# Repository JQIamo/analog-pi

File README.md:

# analog-pi
Analog PI controller with > 10MHz bandwidth. Design by Joe Tiamsuphat.

For full documentation of the circuit, see the [manual](https://github.com/JQIamo/analog-pi/blob/master/pi/Documents/PI_Manual.pdf).
Please read the manual very carefully, especially the section "Initial Calibration" at page 14. A wrong calibration could result in damaging the circuit's output stages.

**NOTE:** The PI controller [manual](https://github.com/JQIamo/analog-pi/blob/master/pi/Documents/PI_Manual.pdf) is out of date. It should still be used as a reference, but it does not document several new features. Please look at issues [#2](https://github.com/JQIamo/analog-pi/issues/2) and [#3](https://github.com/JQIamo/analog-pi/issues/3) for more information. 

## File description

* `/fab/*`: Ready-made files for immediate fabrication. There is the main PI board (`pi_v2.5.3`), and three "shield" boards which make assembly into the box (located in `/fab/EnclosureDesign_v2.5.3_CAD`) easier. See below for description.
* `/pi/*`: Design files for the main PI board, including documentation, schematics, simulations, etc. The schematic/board layout are done in NI Multisim + Ultiboard.
* `/pi-frontpanel/*`: Eagle board files for a frontpanel "shield" board
* `/pi-pots/*`: Eagle board files for potentiometers which set the gains, output offset, sweep amplitude.
* `/pi-shield/*`: Eagle board file for adapter shield between PI board and the POTs/Frontpanel breakout boards.

Total cost is in the neighborhood of $1k per completed box (includes professionally populated PCBs, enclosure, power supply, etc.), although that number would depend on quantity ordered, whether you populate the boards yourself, etc.

## Enclosure

There is a Protocase Designer file (in `/fab/EnclosureDesign_v2.5.3_CAD`

Other auxiliary parts:

| Name | Part number | supplier |
|-------|------------|-------|
| FuseDrawer | 486-1342-ND | Digikey|
|Fuse	|F2393-ND|	Digikey|
|PwrEntry	|486-1302-ND	|Digikey
HexStandoff	|36-4802-ND|	Digikey
KnurledKnob	|226-3084-ND	|Digikey
POT Dial|	987-1002-ND	|Digikey
Isolated BNC	|ARFX1905-ND	|Digikey
PowerSupply	|179-2302-ND|	Digikey

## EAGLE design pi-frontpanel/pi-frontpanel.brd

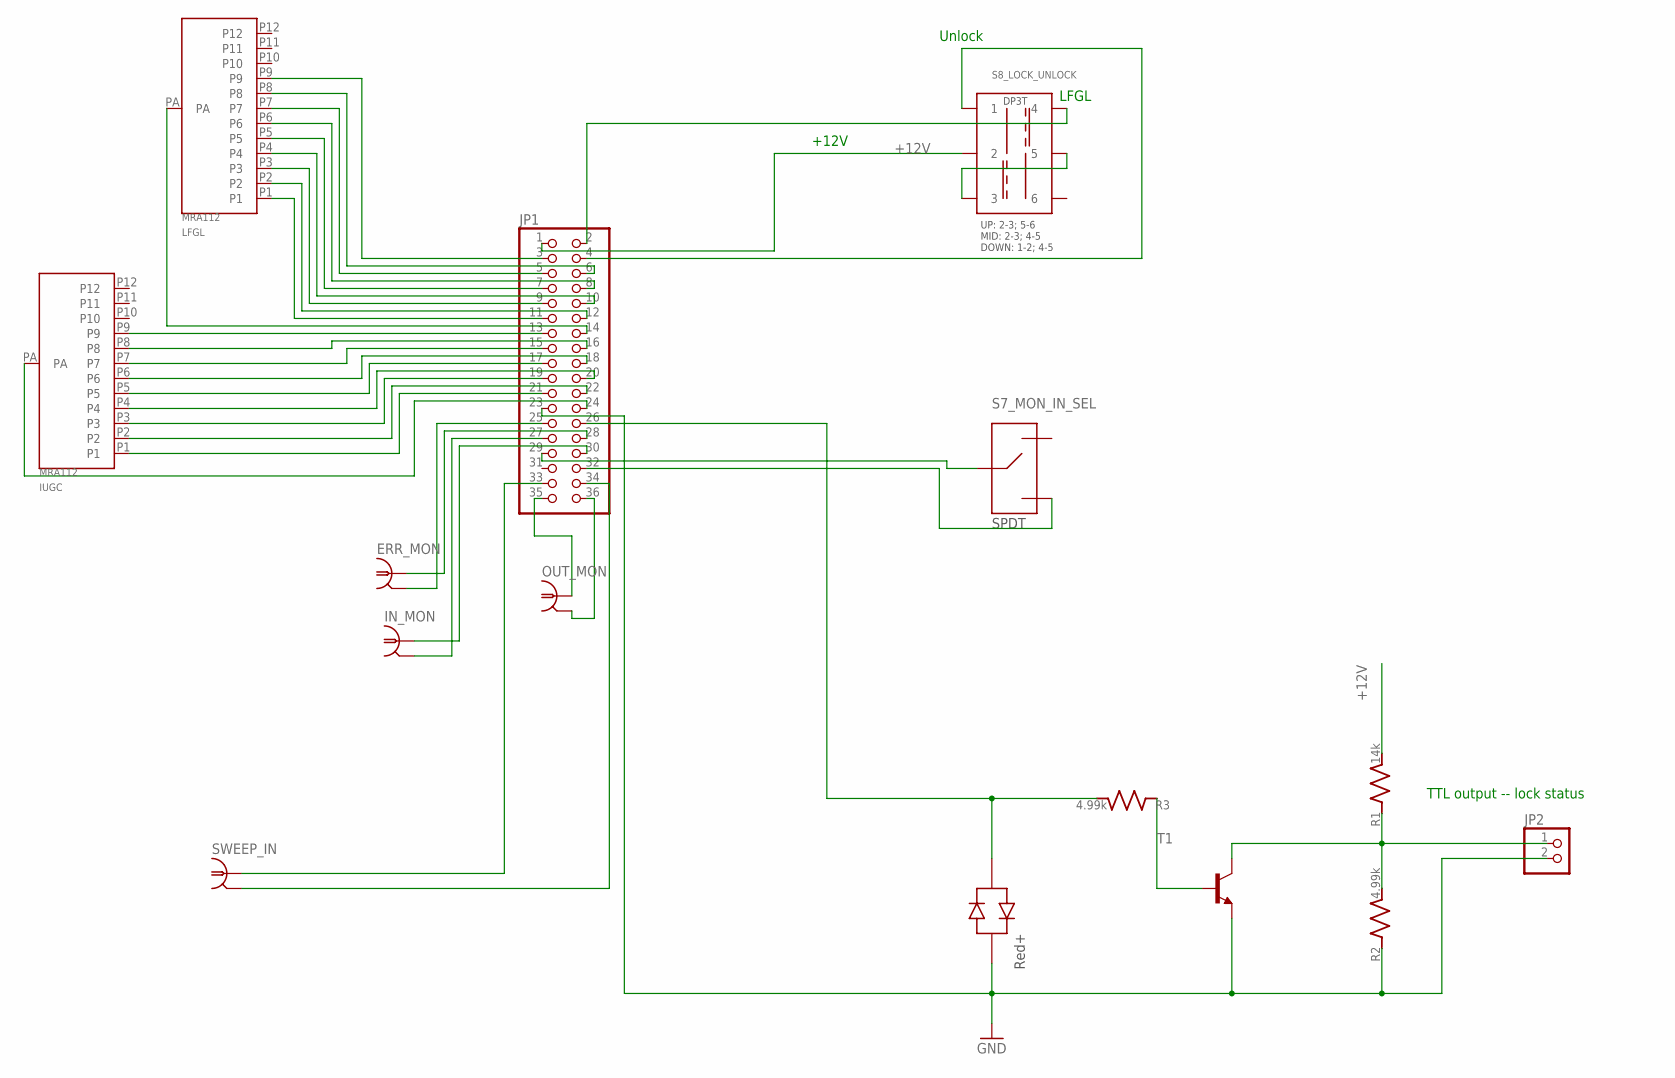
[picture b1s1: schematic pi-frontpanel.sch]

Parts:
ERR_MON: BNC-V; PARTNO A32262-ND
IN_MON: BNC-V; PARTNO A32262-ND
IUGC: MRA112; PARTNO 360-2368-ND
JP1: PINHD-2X18; 2X18; PARTNO S7086-ND
JP2: PINHD-1X2; 1X02; PARTNO A1921-ND
LED: SSL-LX5093IGW; LED-TH; PARTNO 67-2207-ND
LFGL: MRA112; PARTNO 360-2368-ND
OUT_MON: BNC-V; PARTNO A32262-ND
R1: 14k; R_1206; PARTNO P14.0KFCT-ND
R2, R3: 4.99k; R_1206; PARTNO P4.99KFCT-ND
S7_MON_IN_SEL: SPDT; SPDT_LUG; PARTNO 450-1523-ND
S8_LOCK_UNLOCK: DP3T; SP3T_LUG
SWEEP_IN: BNC-V; PARTNO A32262-ND
T1: MMBT2222ALT1-NPN-SOT23-BEC; SOT23-BEC; PARTNO MMBT2222A-FDICT-ND

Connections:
+12V: JP1.1, R1.P$2 (2), S8_LOCK_UNLOCK.2
GND: JP1.23, JP2.2, LED.P$2 (RED+), R2.P$1 (1), T1.E
unnamed: S8_LOCK_UNLOCK.3, S8_LOCK_UNLOCK.5
unnamed: JP1.3, LFGL.P9
unnamed: JP2.1, R1.P$1 (1), R2.P$2 (2), T1.C
unnamed: R3.P$1 (1), T1.B
unnamed: JP1.26, LED.P$1 (GREEN+), R3.P$2 (2)
unnamed: JP1.6, LFGL.P8
unnamed: JP1.5, LFGL.P7
unnamed: JP1.8, LFGL.P6
unnamed: JP1.7, LFGL.P5
unnamed: JP1.10, LFGL.P4
unnamed: JP1.11, LFGL.P1
unnamed: JP1.9, LFGL.P3
unnamed: JP1.12, LFGL.P2
unnamed: IUGC.P9, JP1.13
unnamed: JP1.14, LFGL.PA
unnamed: IUGC.P8, JP1.16
unnamed: IUGC.P7, JP1.15
unnamed: IUGC.P6, JP1.18
unnamed: IUGC.P5, JP1.17
unnamed: IUGC.P4, JP1.20
unnamed: IUGC.P3, JP1.19
unnamed: IUGC.P2, JP1.22
unnamed: IUGC.P1, JP1.21
unnamed: IUGC.PA, JP1.24
unnamed: IN_MON.2, JP1.27
unnamed: IN_MON.1, JP1.30
unnamed: ERR_MON.2, JP1.25
unnamed: ERR_MON.1, JP1.28
unnamed: JP1.36, OUT_MON.2
unnamed: JP1.35, OUT_MON.1
unnamed: JP1.34, SWEEP_IN.2
unnamed: JP1.33, SWEEP_IN.1
unnamed: JP1.29, S7_MON_IN_SEL.2
unnamed: JP1.32, S7_MON_IN_SEL.3
unnamed: JP1.2, S8_LOCK_UNLOCK.4
unnamed: JP1.4, S8_LOCK_UNLOCK.1

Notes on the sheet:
+12V
LFGL
Unlock
TTL output -- lock status

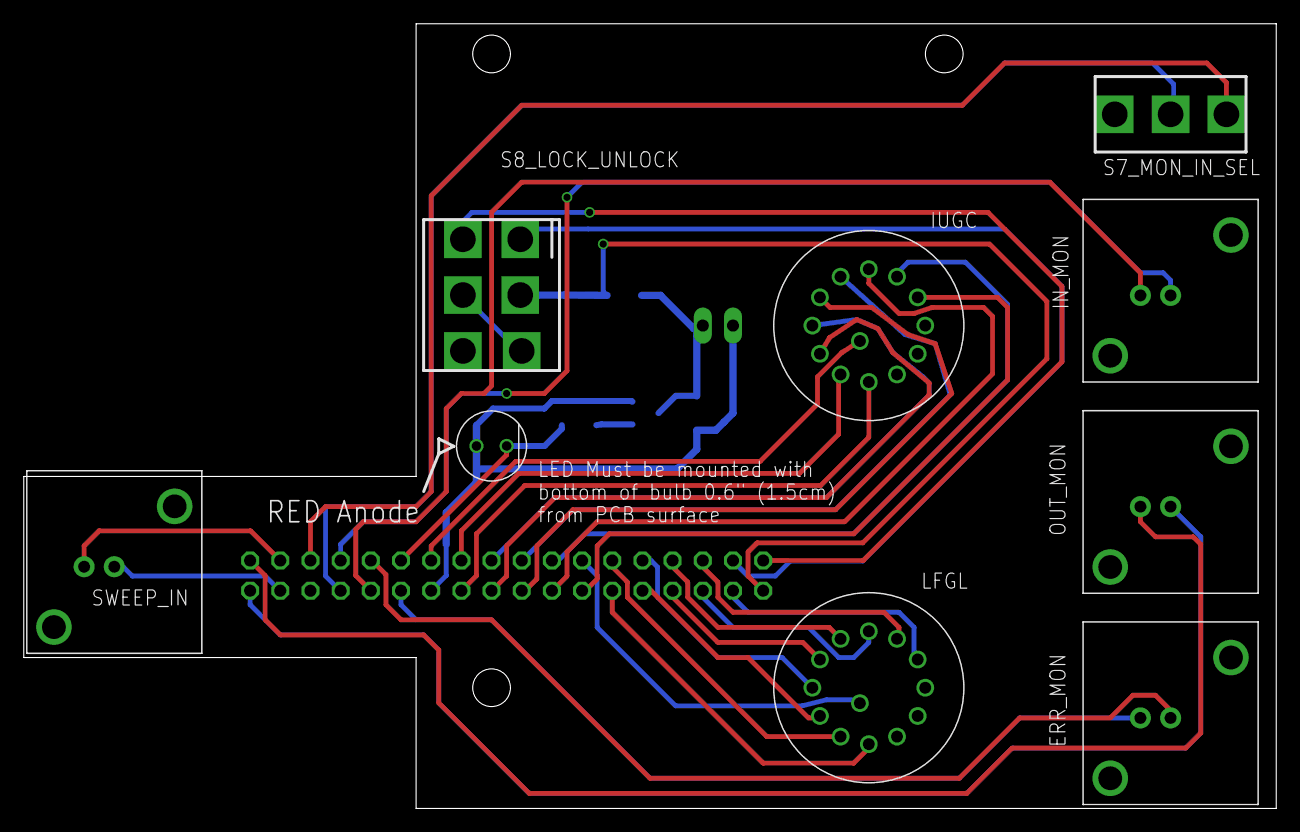
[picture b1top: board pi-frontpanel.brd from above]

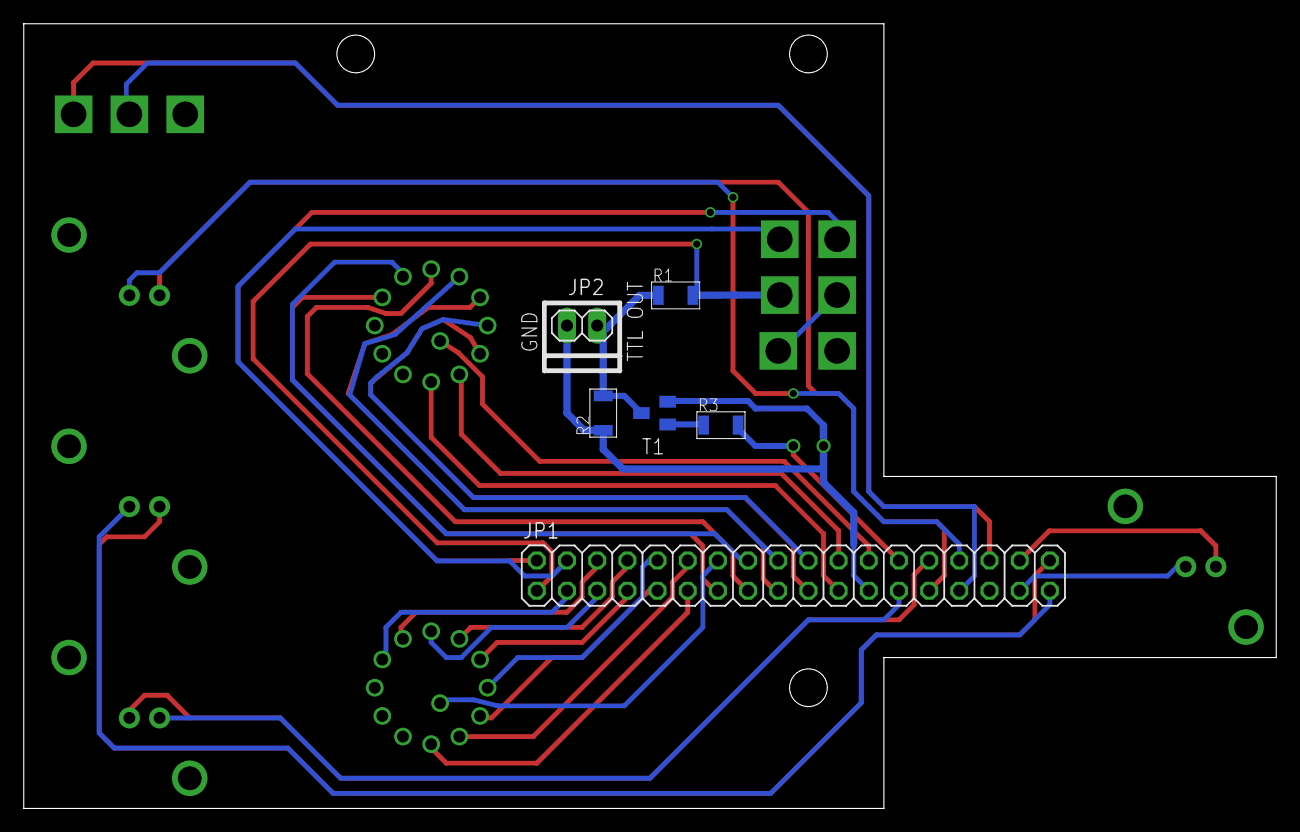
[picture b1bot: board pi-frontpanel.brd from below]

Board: 2 copper layers, 105.4 x 66.0 mm, 15 parts (6 on the bottom side), 38 nets.

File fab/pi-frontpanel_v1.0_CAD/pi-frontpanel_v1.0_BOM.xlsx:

Line | Qty | Value | Part Num | Source | Package | Parts | Notes
1.0 | 1.0 |  | 450-1536-ND | Digikey | SP3T_LUG | S8_LOCK_UNLOCK
2.0 | 1.0 |  | A1921-ND | Digikey | 1X02 | JP2
3.0 | 1.0 |  | MMBT2222A-FDICT-ND | Digikey | SOT23-BEC | T1
4.0 | 1.0 |  | S7086-ND | Digikey | 2X18 | JP1
5.0 | 2.0 | 4.99k | P4.99KFCT-ND | Digikey | R_1206 | R2, R3
6.0 | 1.0 | 14k | P14.0KFCT-ND | Digikey | R_1206 | R1
7.0 | 4.0 | BNC-V | A32262-ND | Digikey | BNC-V | ERR_MON, IN_MON, OUT_MON, SWEEP_IN
8.0 | 2.0 | MRA112 | 360-2368-ND | Digikey | MRA112 | IUGC, LFGL
9.0 | 1.0 | SPDT | 450-1523-ND | Digikey | SPDT_LUG | S7_MON_IN_SEL
10.0 | 1.0 | SSL-LX5093IGW | 67-2207-ND | Digikey | LED-TH | LED | This part needs to be soldered such that the bottom of the LED is 0.6" (1.5cm) 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

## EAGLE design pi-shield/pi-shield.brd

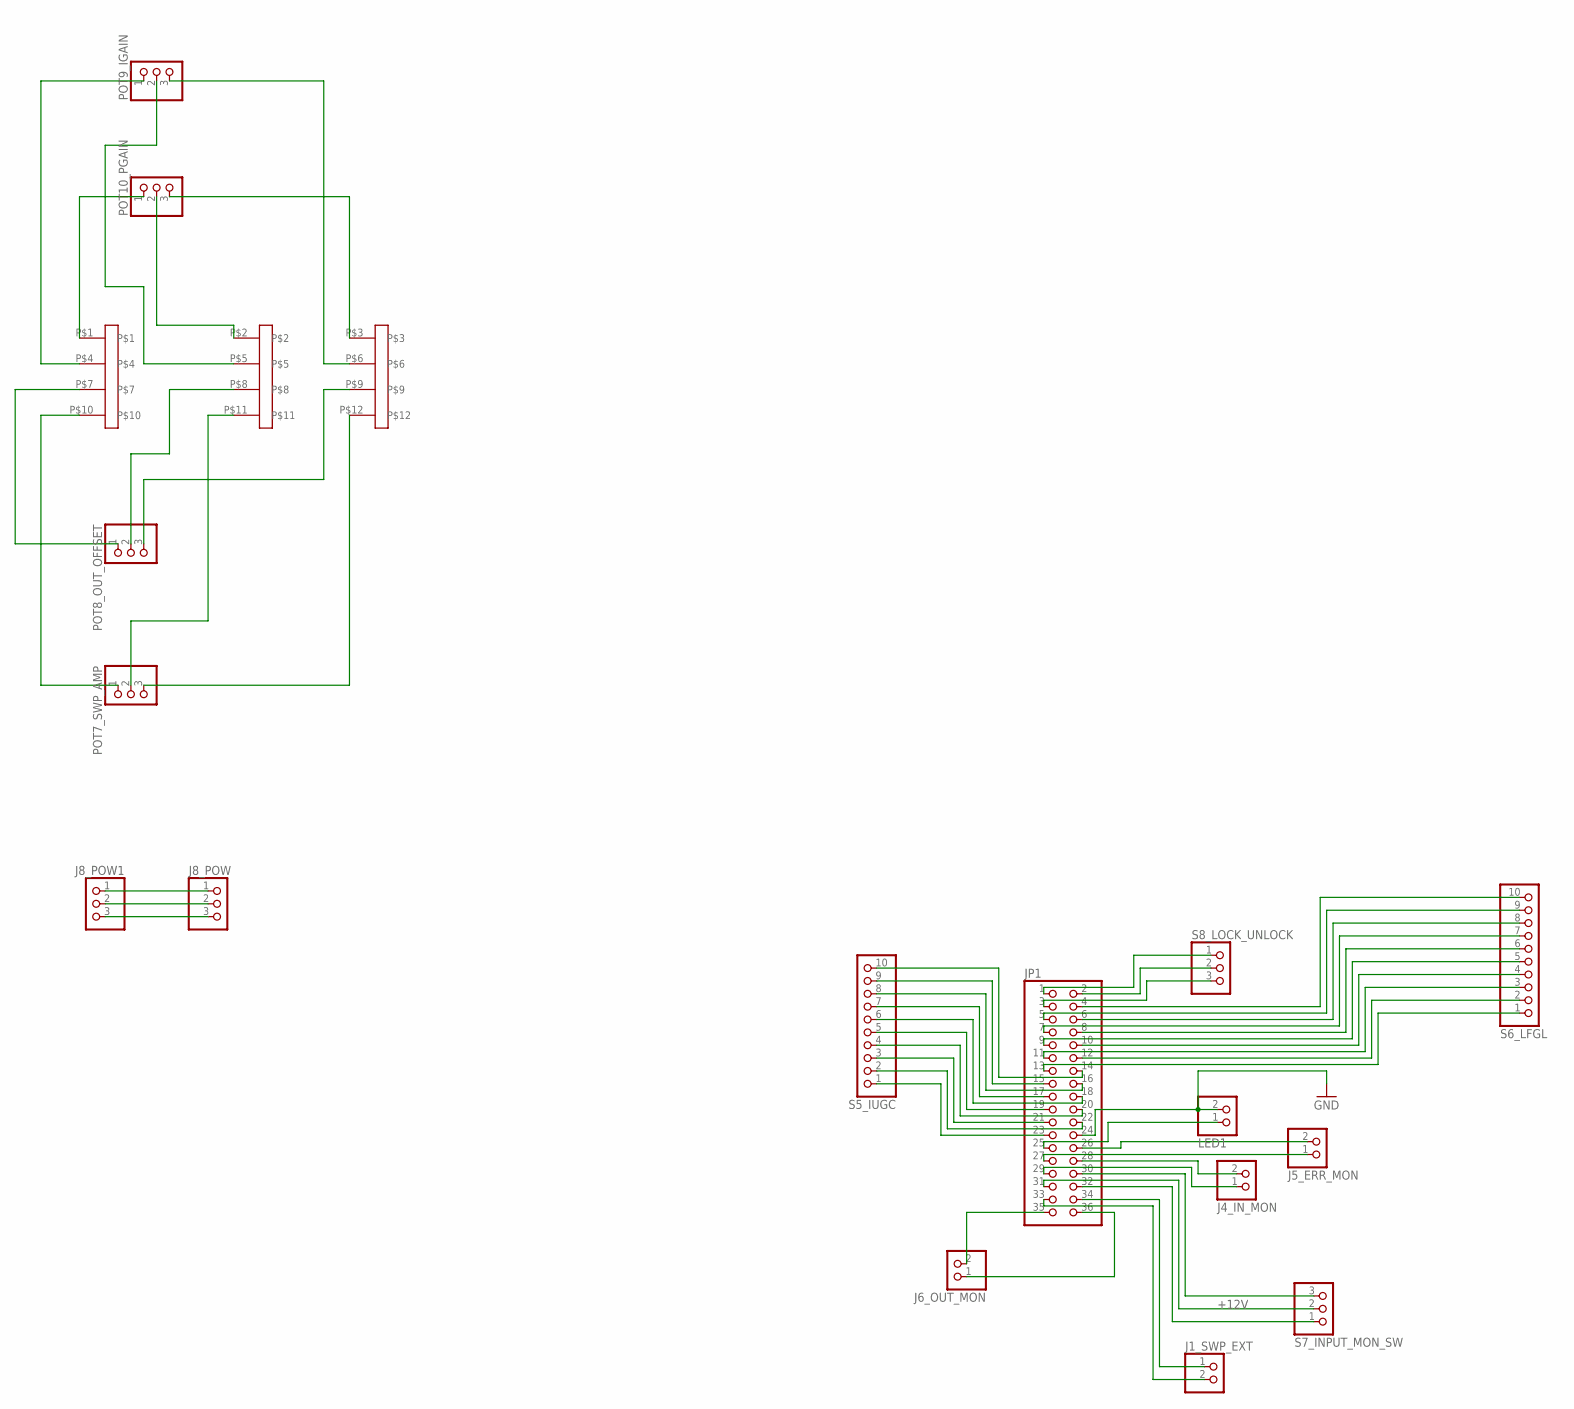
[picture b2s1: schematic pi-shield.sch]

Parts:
J1: PINHD-3X4; 3X04; PARTNO S7071-ND (2x)
J1_SWP_EXT, J4_IN_MON, J5_ERR_MON, J6_OUT_MON: PINHD-1X2; 1X02; PARTNO S7000-ND
J8_POW: PINHD-1X3; 1X03; PARTNO S7036-ND
J8_POW1: PINHD-1X3; 1X03; PARTNO A19470-ND
JP1: PINHD-2X18/90; 2X18/90; PARTNO S2111EC-18-ND
LED1: PINHD-1X2; 1X02; PARTNO S7000-ND
POT7_SWP_AMP, POT8_OUT_OFFSET, POT9_IGAIN, POT10_PGAIN: PINHD-1X3; 1X03; PARTNO S7036-ND
S5_IUGC, S6_LFGL: PINHD-1X10; 1X10; PARTNO S7008-ND
S7_INPUT_MON_SW, S8_LOCK_UNLOCK: PINHD-1X3; 1X03; PARTNO S7036-ND

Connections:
+12V: JP1.31, S7_INPUT_MON_SW.2
GND: JP1.24, LED1.2
unnamed: J8_POW.1, J8_POW1.1
unnamed: J8_POW.2, J8_POW1.2
unnamed: J8_POW.3, J8_POW1.3
unnamed: J1.P$1, POT10_PGAIN.1
unnamed: J1.P$2, POT10_PGAIN.2
unnamed: J1.P$3, POT10_PGAIN.3
unnamed: J1.P$4, POT9_IGAIN.1
unnamed: J1.P$5, POT9_IGAIN.2
unnamed: J1.P$6, POT9_IGAIN.3
unnamed: J1.P$7, POT8_OUT_OFFSET.1
unnamed: J1.P$8, POT8_OUT_OFFSET.2
unnamed: J1.P$9, POT8_OUT_OFFSET.3
unnamed: J1.P$10, POT7_SWP_AMP.1
unnamed: J1.P$11, POT7_SWP_AMP.2
unnamed: J1.P$12, POT7_SWP_AMP.3
unnamed: J1_SWP_EXT.1, JP1.34
unnamed: J1_SWP_EXT.2, JP1.33
unnamed: J5_ERR_MON.2, JP1.26
unnamed: J5_ERR_MON.1, JP1.27
unnamed: J4_IN_MON.2, JP1.28
unnamed: J4_IN_MON.1, JP1.29
unnamed: JP1.30, S7_INPUT_MON_SW.3
unnamed: JP1.32, S7_INPUT_MON_SW.1
unnamed: JP1.4, S6_LFGL.10
unnamed: JP1.5, S6_LFGL.9
unnamed: JP1.6, S6_LFGL.8
unnamed: JP1.7, S6_LFGL.7
unnamed: JP1.8, S6_LFGL.6
unnamed: JP1.9, S6_LFGL.5
unnamed: JP1.10, S6_LFGL.4
unnamed: JP1.11, S6_LFGL.3
unnamed: JP1.12, S6_LFGL.2
unnamed: JP1.13, S6_LFGL.1
unnamed: JP1.14, S5_IUGC.10
unnamed: JP1.15, S5_IUGC.9
unnamed: JP1.1, S8_LOCK_UNLOCK.1
unnamed: JP1.16, S5_IUGC.8
unnamed: JP1.17, S5_IUGC.7
unnamed: JP1.18, S5_IUGC.6
unnamed: JP1.19, S5_IUGC.5
unnamed: JP1.20, S5_IUGC.4
unnamed: JP1.21, S5_IUGC.3
unnamed: JP1.22, S5_IUGC.2
unnamed: JP1.23, S5_IUGC.1
unnamed: JP1.25, LED1.1
unnamed: JP1.2, S8_LOCK_UNLOCK.2
unnamed: JP1.3, S8_LOCK_UNLOCK.3
unnamed: J6_OUT_MON.2, JP1.35
unnamed: J6_OUT_MON.1, JP1.36

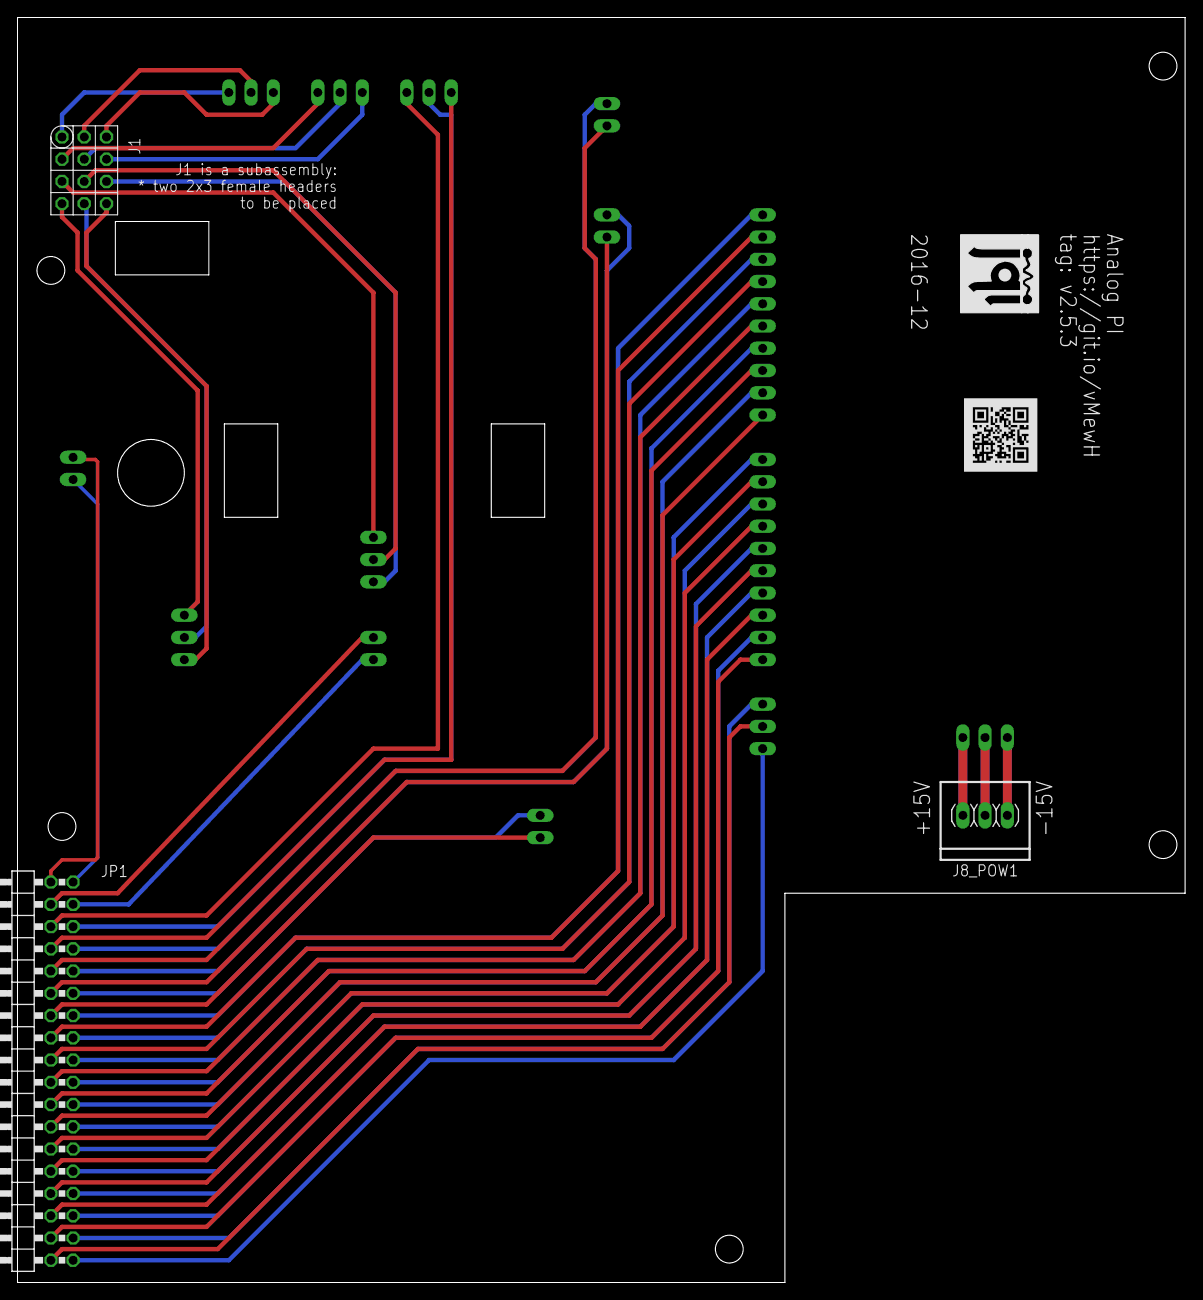
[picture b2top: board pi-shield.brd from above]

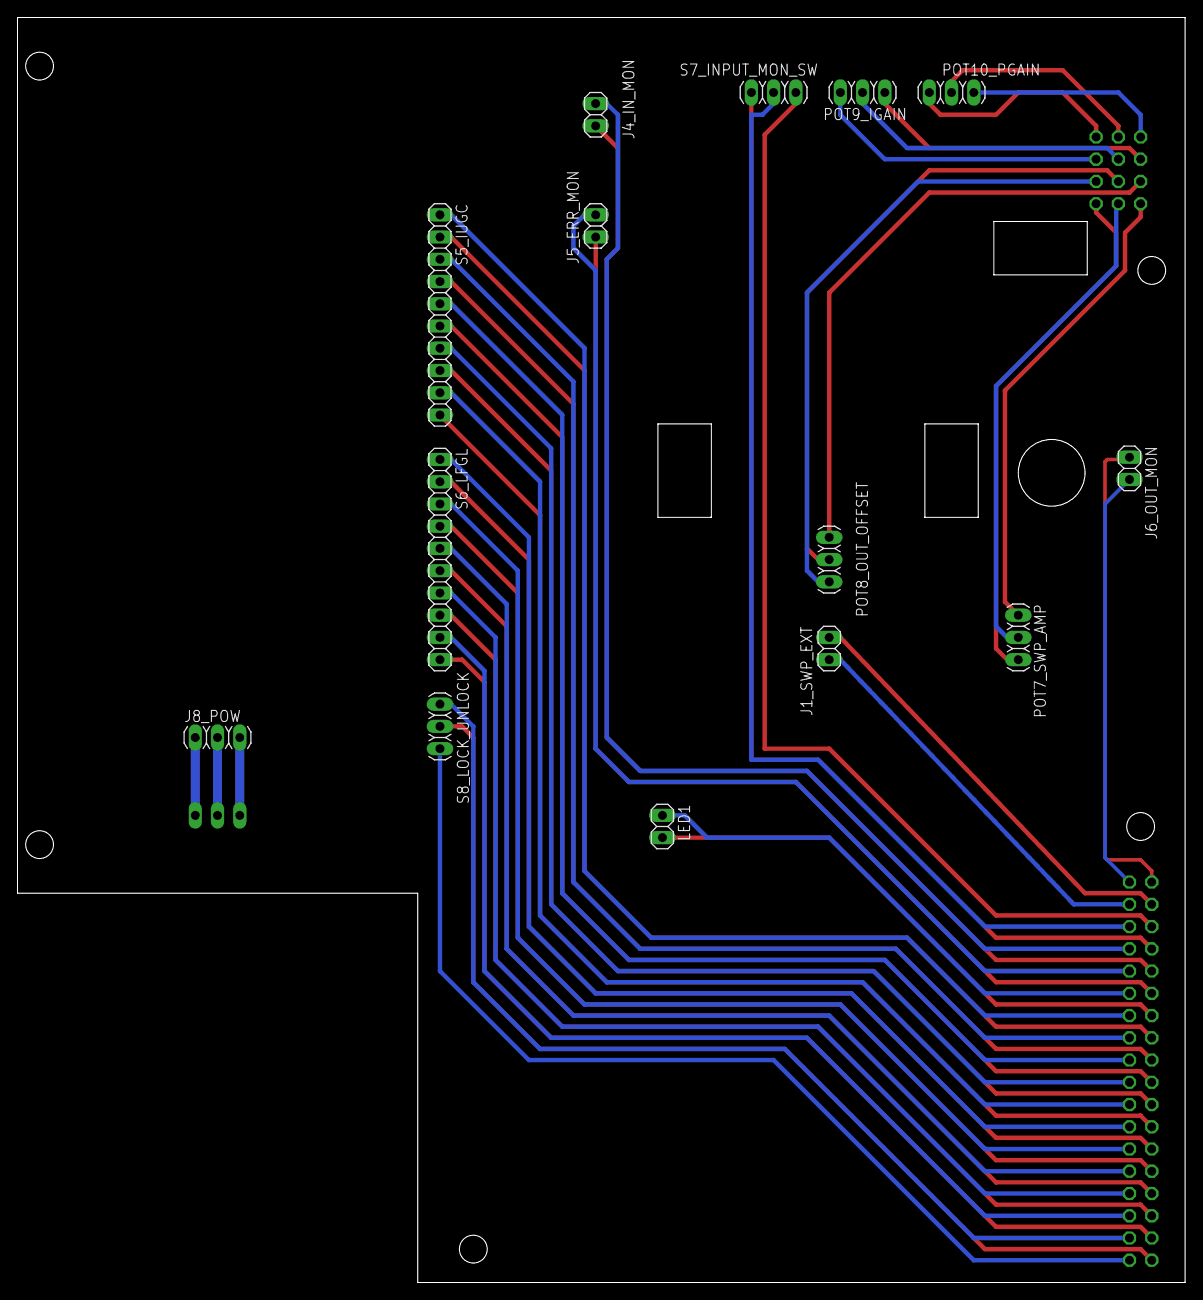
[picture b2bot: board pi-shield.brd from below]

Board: 2 copper layers, 133.3 x 144.4 mm, 19 parts (14 on the bottom side), 51 nets.

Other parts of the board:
U$1: QR-HTTPS://GIT.IO/VMEWH-LIGHT-SILK
U$2: JQI_LOGO_NEGATIVE-SILKSCREEN

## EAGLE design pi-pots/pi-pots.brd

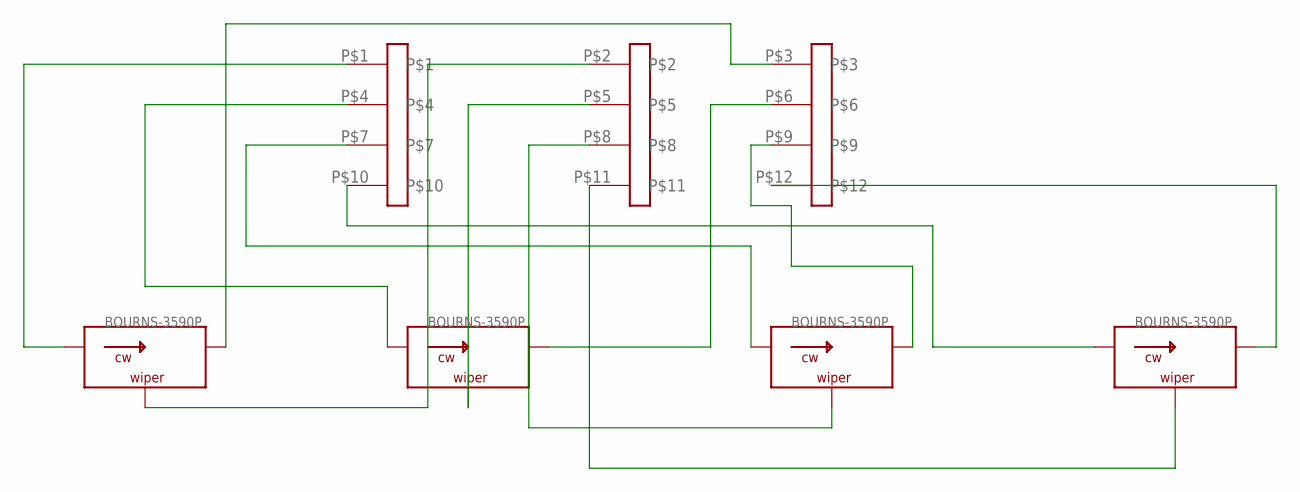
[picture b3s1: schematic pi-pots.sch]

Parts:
I_GAIN: BOURNS-3590P; 3590P; PARTNO 3590P-1-103L-ND
J1: PINHD-3X4; 3X04; PARTNO 952-2121-ND (2x)
OUTPUT_OFFSET: BOURNS-3590P; 3590P; PARTNO 3590P-1-103L-ND
P_GAIN: BOURNS-3590P; 3590P; PARTNO 3590P-1-103L-ND
SWEEP_AMP: BOURNS-3590P; 3590P; PARTNO 3590P-1-103L-ND

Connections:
unnamed: J1.P$1, P_GAIN.1
unnamed: I_GAIN.1, J1.P$4
unnamed: J1.P$7, OUTPUT_OFFSET.1
unnamed: J1.P$10, SWEEP_AMP.1
unnamed: J1.P$2, P_GAIN.2
unnamed: I_GAIN.2, J1.P$5
unnamed: J1.P$8, OUTPUT_OFFSET.2
unnamed: J1.P$11, SWEEP_AMP.2
unnamed: J1.P$3, P_GAIN.3
unnamed: I_GAIN.3, J1.P$6
unnamed: J1.P$9, OUTPUT_OFFSET.3
unnamed: J1.P$12, SWEEP_AMP.3

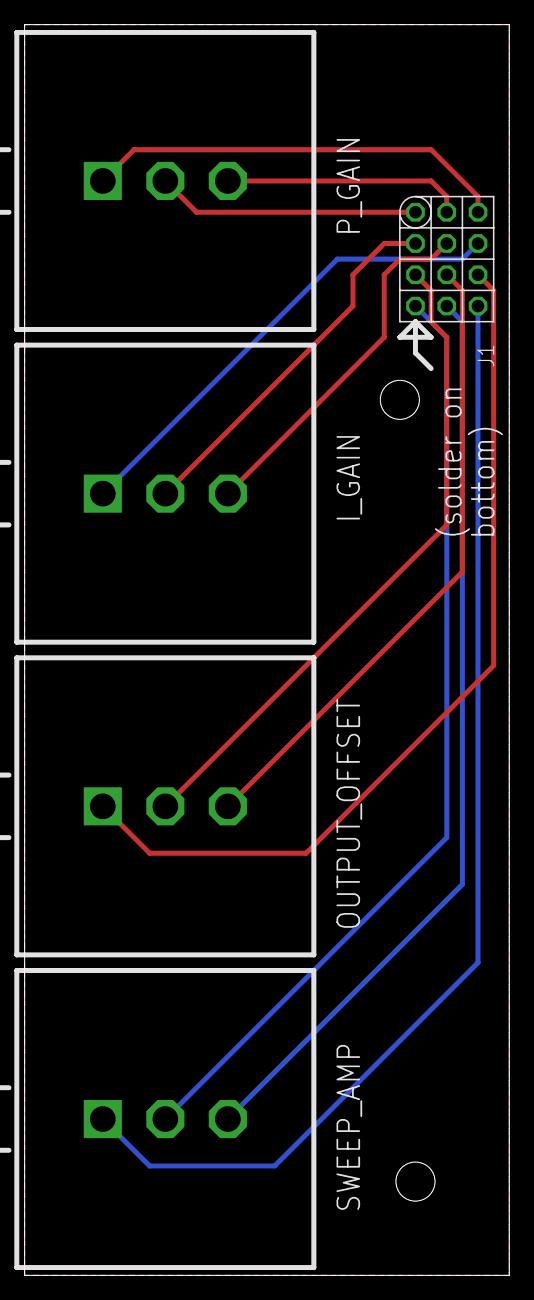
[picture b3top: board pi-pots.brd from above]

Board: 2 copper layers, 39.4 x 101.6 mm, 5 parts (0 on the bottom side), 12 nets.

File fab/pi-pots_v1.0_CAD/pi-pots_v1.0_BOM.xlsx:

Line | Qty | Value | Part Num | Source | Package | Parts | Notes
1.0 | 4.0 | BOURNS-3590P | 3590P-1-103L-ND | Digikey | SP3T_LUG | I_GAIN, OUTPUT_OFFSET, P_GAIN, SWEEP_AMP
2.0 | 2.0 | PINHD-3X4 | 952-2121-ND | Digikey | 3x02 | J1 | This is a subassembly. Two 3x2 male headers are placed on bottom as marked on P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

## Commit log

2017-06-13 Added current snapshot of project
2017-06-13 added screenshot of enclosure
2017-06-13 updated readme with more information
2018-04-10 Removed outdated gerber files and added drill file
2018-04-11 Added LICENSE - CERN OHWL v1.2
2019-12-13 Calibration Windows
    I've opened up windows above POT1-3 and U9, pin 10. The windows allow access to the pots and U9 for initial calibration of the PI controller.
    DSB
